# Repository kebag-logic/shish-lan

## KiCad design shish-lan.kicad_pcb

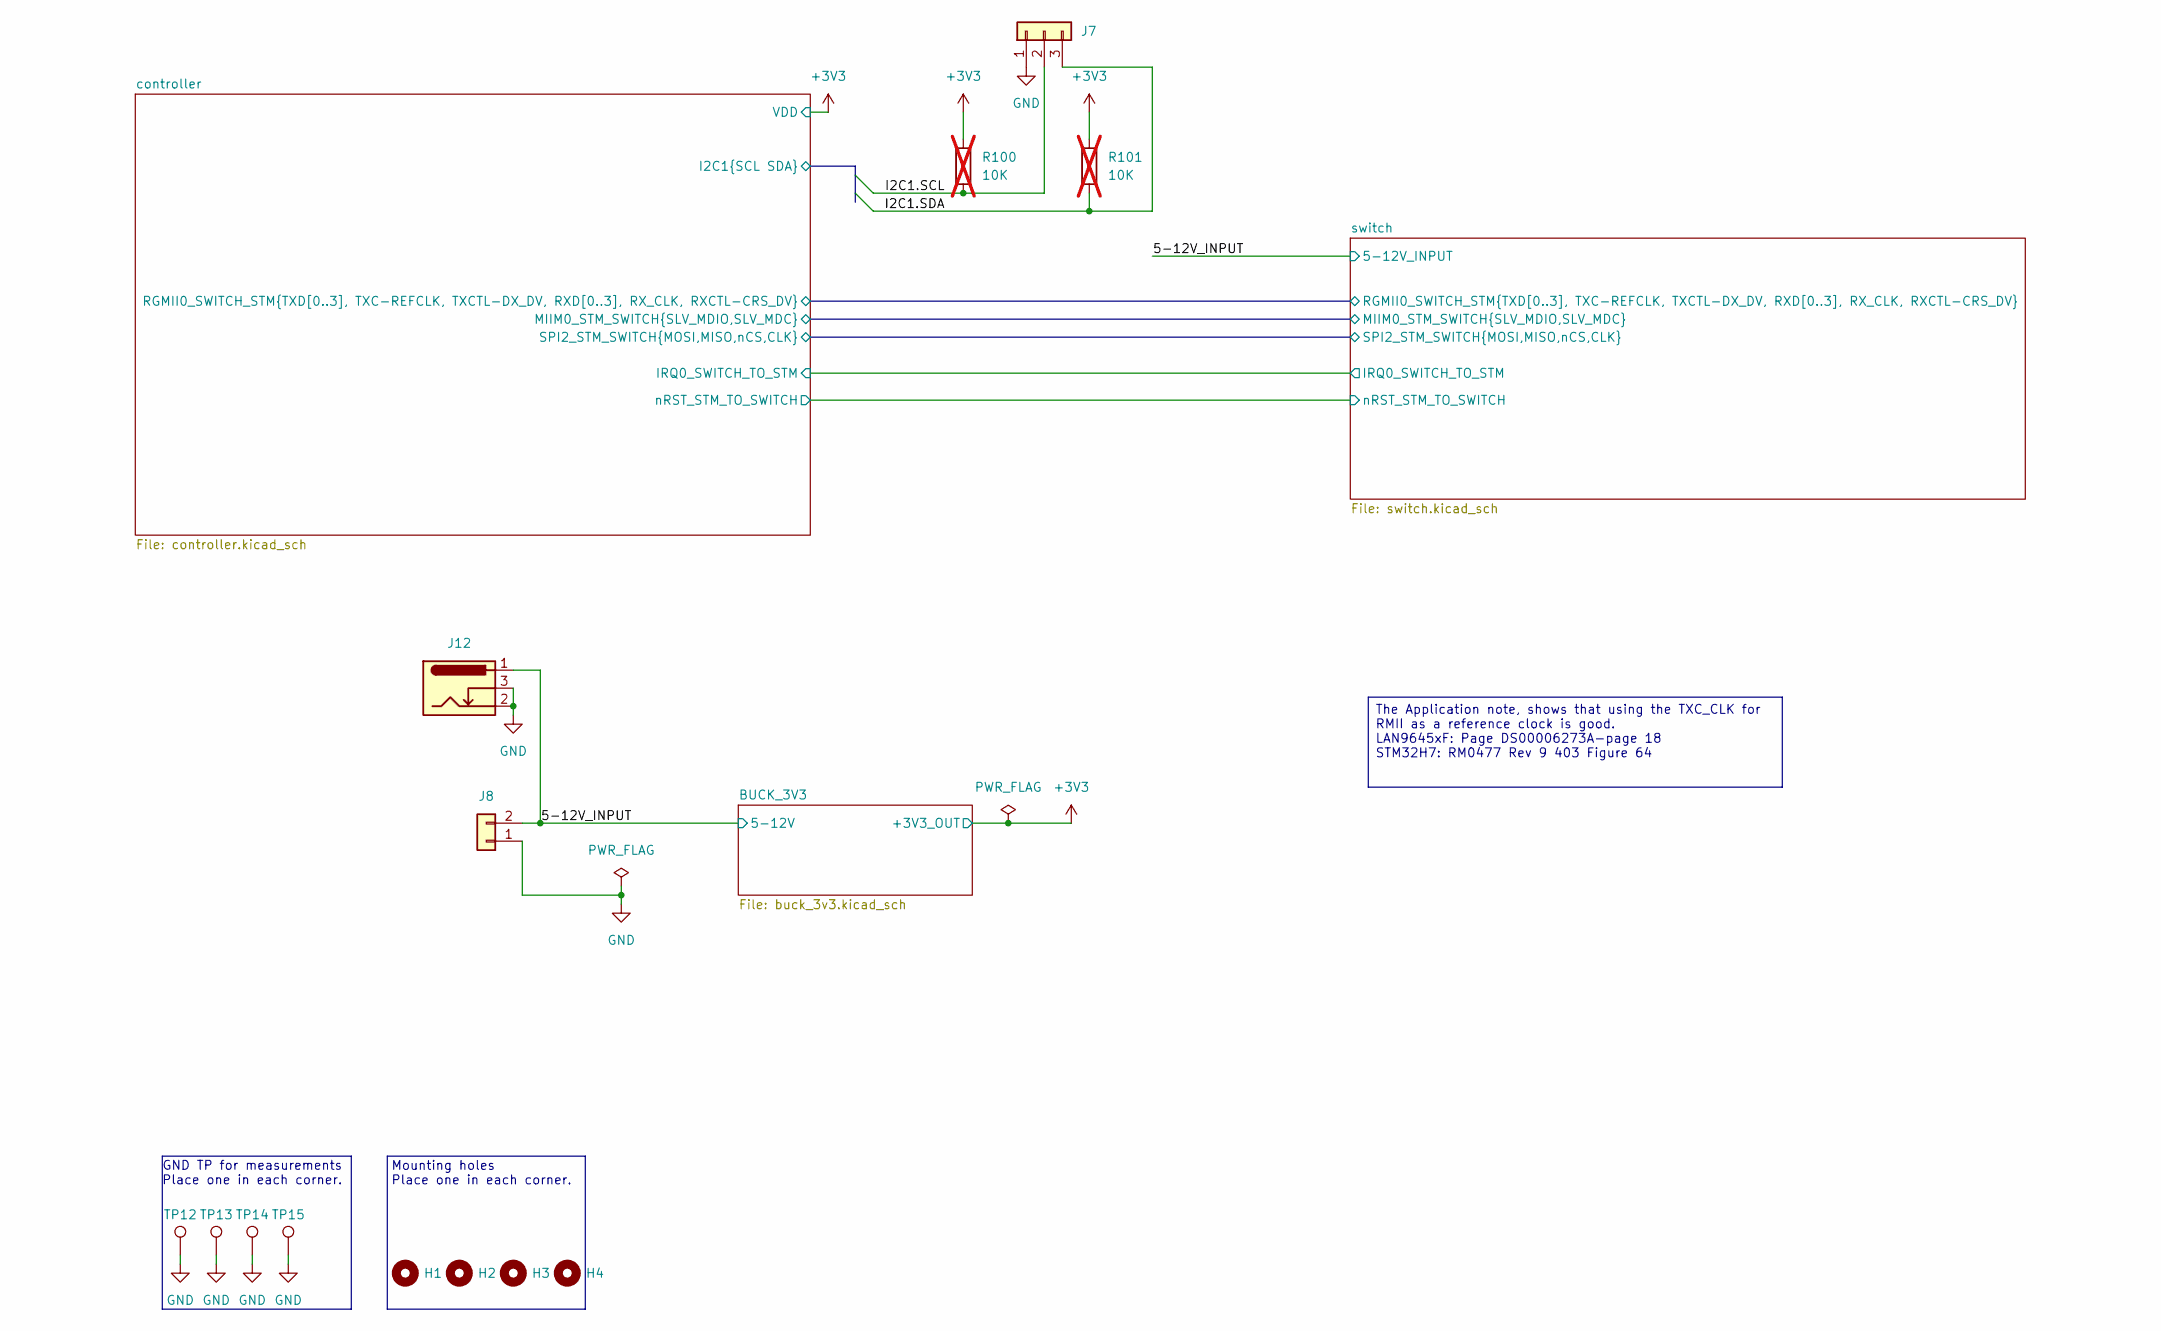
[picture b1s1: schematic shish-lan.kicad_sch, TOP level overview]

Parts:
H1, H2, H3, H4: MountingHole_M3; MountingHole_3.2mm_M3_Pad
J7: Header_03x01_2.54mm_0mm_Straight; 03x01_2.54mm_Header; MPN 87224-3; Mouser 571-872243
J8: Header_02x01_2.54mm_0mm_Straight; 02x01_2.54mm_Header; MPN 87224-2; Mouser 571-872242
J12: DC-Jack_Wuerth_694108301002; MPN 694108301002; Mouser 710-694108301002
R100, R101: 10K; R_0603; Tolerance_in_pct 5; MPN CRCW060310K0JNEC; Mouser 71-CRCW060310K0JNEC; not fitted
TP12, TP13, TP14, TP15: TestPoint

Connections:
/5-12V_INPUT: J8.2, J12.1; also elsewhere on the board
/controller/I2C1.SCL: J7.2, R100.2; also elsewhere on the board
/controller/I2C1.SDA: J7.3, R101.2; also elsewhere on the board

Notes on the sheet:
Mounting holes Place one in each corner.
GND TP for measurements Place one in each corner.
The Application note, shows that using the TXC_CLK for RMII as a reference clock is good. LAN9645xF: Page DS00006273A-page 18 STM32H7: RM0477 Rev 9 403 Figure 64

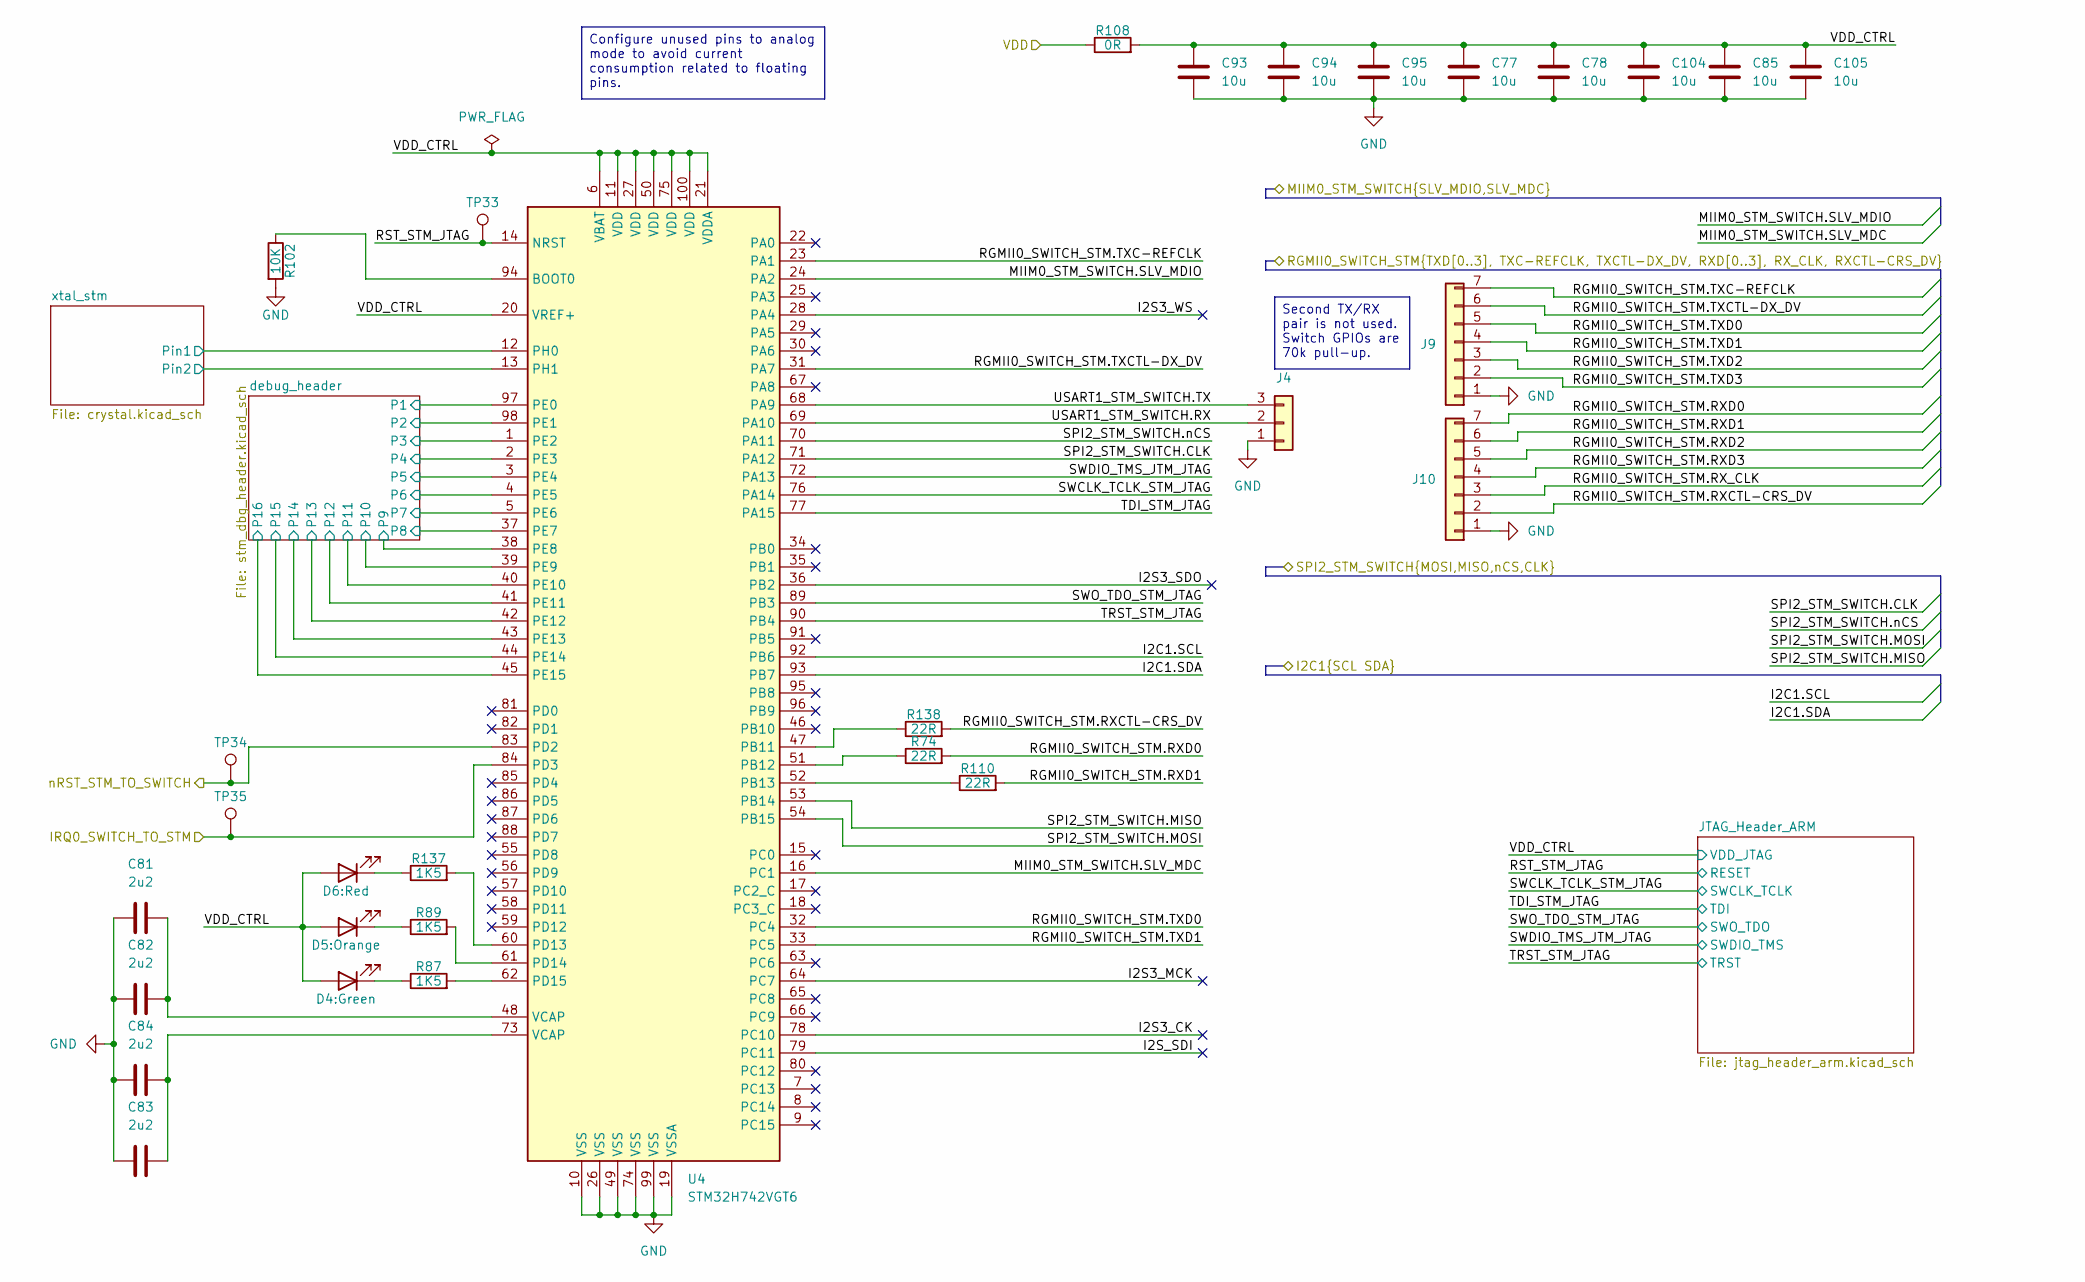
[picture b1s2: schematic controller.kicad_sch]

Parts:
C77, C78, C85, C93, C94, C95, C104, C105: 10u; C_0603; Voltage_in_V 25; Tolerance_in_pct 20; MPN CL10A106MA8NRNC; Mouser 187-CL10A106MA8NRNC
C81, C82, C83, C84: 2u2; C_0603; Voltage_in_V 35; Tolerance_in_pct 20; MPN GRM188R6YA225MA12D; Mouser 81-GRM188R6YA225MA2D
D4: LED_{color}_{U_F}_{I_F}; LED_0603; MPN LTST-C190GKT; Mouser 859-LTST-C190GKT
D5: LED_{color}_{U_F}_{I_F}; LED_0603; MPN LTST-C190KFKT; Mouser 859-LTST-C190KFKT
D6: LED_{color}_{U_F}_{I_F}; LED_0603; MPN LTST-C194KRKT; Mouser 859-LTST-C194KRKT
J4: Header_03x01_2.54mm_0mm_Straight; 03x01_2.54mm_Header; MPN 87224-3; Mouser 571-872243
J9, J10: Header_07x01_2.54mm_0mm_Straight; 07x01_2.54mm_Header; MPN TLW-107-06-G-S; Mouser 200-TLW10706GS
R74, R110, R138: 22R; R_0603; Tolerance_in_pct 1; MPN RC0603FR-1022RL; Mouser 603-RC0603FR-1022RL
R87, R89, R137: 1K5; R_0603; Tolerance_in_pct 5; MPN AC0603JR-071K5L; Mouser 603-AC0603JR-071K5L
R102: 10K; R_0603; Tolerance_in_pct 5; MPN CRCW060310K0JNEC; Mouser 71-CRCW060310K0JNEC
R108: 0R; R_2512; Tolerance_in_pct 5; MPN CRF2512-J/-000ELF; Mouser 652-CRF2512-J-000ELF
TP33, TP34, TP35: TestPoint
U4: STM32H742VGT6; LQFP-100_14x14mm_P0.5mm; MPN STM32H742VGT6; Mouser 511-STM32H742VGT6

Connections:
/controller/I2C1.SCL: U4.92 (PB6); also elsewhere on the board
/controller/I2C1.SDA: U4.93 (PB7); also elsewhere on the board
/controller/I2S3_CK: U4.78 (PC10)
/controller/I2S3_MCK: U4.64 (PC7)
/controller/I2S3_SDO: U4.36 (PB2)
/controller/I2S3_WS: U4.28 (PA4)
/controller/I2S_SDI: U4.79 (PC11)
/controller/MIIM0_STM_SWITCH.SLV_MDC: U4.16 (PC1); also elsewhere on the board
/controller/MIIM0_STM_SWITCH.SLV_MDIO: U4.24 (PA2); also elsewhere on the board
/controller/RGMII0_SWITCH_STM.RXCTL-CRS_DV: J10.2, R138.2; also elsewhere on the board
/controller/RGMII0_SWITCH_STM.RXD0: J10.7 (Pin_3), R74.2; also elsewhere on the board
/controller/RGMII0_SWITCH_STM.RXD1: J10.6 (Pin_3), R110.2; also elsewhere on the board
/controller/RGMII0_SWITCH_STM.RXD2: J10.5 (Pin_2); also elsewhere on the board
/controller/RGMII0_SWITCH_STM.RXD3: J10.4 (Pin_1); also elsewhere on the board
/controller/RGMII0_SWITCH_STM.RX_CLK: J10.3; also elsewhere on the board
/controller/RGMII0_SWITCH_STM.TXC-REFCLK: J9.7 (Pin_3), U4.23 (PA1); also elsewhere on the board
/controller/RGMII0_SWITCH_STM.TXCTL-DX_DV: J9.6 (Pin_3), U4.31 (PA7); also elsewhere on the board
/controller/RGMII0_SWITCH_STM.TXD0: J9.5 (Pin_2), U4.32 (PC4); also elsewhere on the board
/controller/RGMII0_SWITCH_STM.TXD1: J9.4 (Pin_1), U4.33 (PC5); also elsewhere on the board
/controller/RGMII0_SWITCH_STM.TXD2: J9.3; also elsewhere on the board
/controller/RGMII0_SWITCH_STM.TXD3: J9.2; also elsewhere on the board
/controller/RST_STM_JTAG: TP33.1 (1_1), U4.14 (NRST); also elsewhere on the board
/controller/SPI2_STM_SWITCH.CLK: U4.71 (PA12); also elsewhere on the board
/controller/SPI2_STM_SWITCH.MISO: U4.53 (PB14); also elsewhere on the board
/controller/SPI2_STM_SWITCH.MOSI: U4.54 (PB15); also elsewhere on the board
/controller/SPI2_STM_SWITCH.nCS: U4.70 (PA11); also elsewhere on the board
/controller/SWCLK_TCLK_STM_JTAG: U4.76 (PA14); also elsewhere on the board
/controller/SWDIO_TMS_JTM_JTAG: U4.72 (PA13); also elsewhere on the board
/controller/SWO_TDO_STM_JTAG: U4.89 (PB3); also elsewhere on the board
/controller/TDI_STM_JTAG: U4.77 (PA15); also elsewhere on the board
/controller/TRST_STM_JTAG: U4.90 (PB4); also elsewhere on the board
/controller/USART1_STM_SWITCH.RX: J4.2, U4.69 (PA10)
/controller/USART1_STM_SWITCH.TX: J4.3, U4.68 (PA9)
/controller/VDD_CTRL: C77.1, C78.1, C85.1, C93.1, C94.1, C95.1, C104.1, C105.1, D4.2 (A), D5.2 (A), D6.2 (A), R108.2, U4.6 (VBAT), U4.11 (VDD), U4.20 (VREF+), U4.21 (VDDA), U4.27 (VDD), U4.50 (VDD), U4.75 (VDD), U4.100 (VDD); also elsewhere on the board
/controller/debug_header/P1: U4.97 (PE0); also elsewhere on the board
/controller/debug_header/P2: U4.98 (PE1); also elsewhere on the board
/controller/debug_header/P3: U4.1 (PE2); also elsewhere on the board
/controller/debug_header/P4: U4.2 (PE3); also elsewhere on the board
/controller/debug_header/P5: U4.3 (PE4); also elsewhere on the board
/controller/debug_header/P6: U4.4 (PE5); also elsewhere on the board
/controller/debug_header/P7: U4.5 (PE6); also elsewhere on the board
/controller/debug_header/P8: U4.37 (PE7); also elsewhere on the board
/controller/debug_header/P9: U4.38 (PE8); also elsewhere on the board
/controller/debug_header/P10: U4.39 (PE9); also elsewhere on the board
/controller/debug_header/P11: U4.40 (PE10); also elsewhere on the board
/controller/debug_header/P12: U4.41 (PE11); also elsewhere on the board
/controller/debug_header/P13: U4.42 (PE12); also elsewhere on the board
/controller/debug_header/P14: U4.43 (PE13); also elsewhere on the board
/controller/debug_header/P15: U4.44 (PE14); also elsewhere on the board
/controller/debug_header/P16: U4.45 (PE15); also elsewhere on the board
/controller/xtal_stm/Pin1: U4.12 (PH0); also elsewhere on the board
/controller/xtal_stm/Pin2: U4.13 (PH1); also elsewhere on the board
/switch/IRQ0_SWITCH_TO_STM: TP35.1 (1_1), U4.84 (PD3); also elsewhere on the board
/switch/nRST_STM_TO_SWITCH: TP34.1 (1_1), U4.83 (PD2); also elsewhere on the board
unnamed: C81.2, C82.2, U4.48 (VCAP)
unnamed: C83.2, C84.2, U4.73 (VCAP)
unnamed: D4.1 (K), R87.1
unnamed: D5.1 (K), R89.1
unnamed: D6.1 (K), R137.1
unnamed: R102.1, U4.94 (BOOT0)
unnamed: R138.1, U4.47 (PB11)
unnamed: R74.1, U4.51 (PB12)
unnamed: R110.1, U4.52 (PB13)
unnamed: R137.2, U4.60 (PD13)
unnamed: R89.2, U4.61 (PD14)
unnamed: R87.2, U4.62 (PD15)

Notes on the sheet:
Second TX/RX pair is not used. Switch GPIOs are 70k pull-up.
Configure unused pins to analog mode to avoid current consumption related to floating pins.

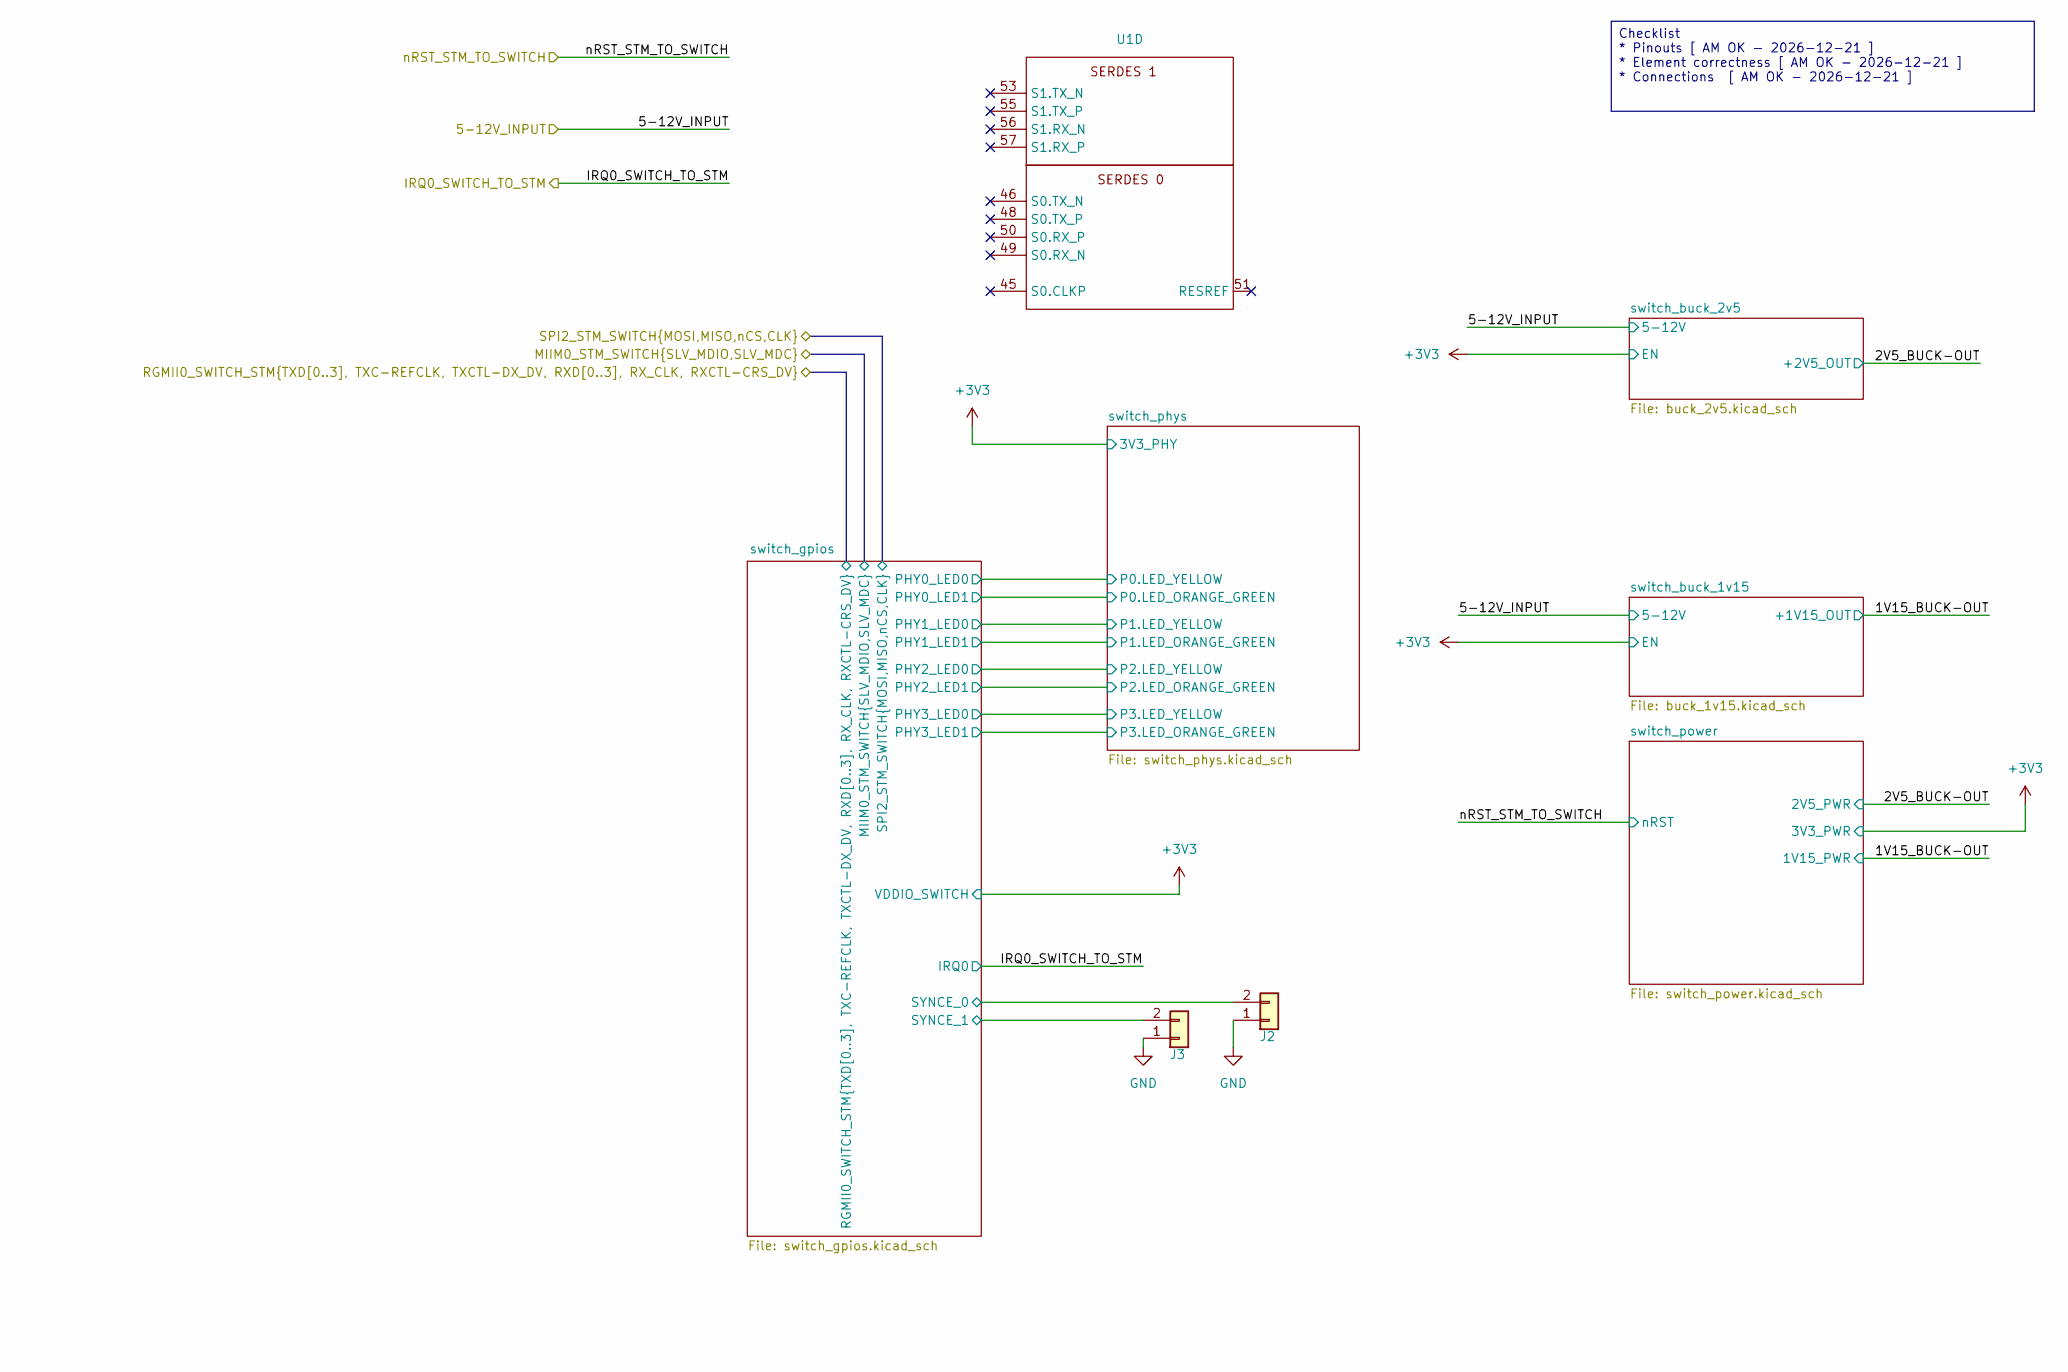
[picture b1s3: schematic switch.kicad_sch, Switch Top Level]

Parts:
J2, J3: Header_02x01_2.54mm_0mm_Straight; 02x01_2.54mm_Header; MPN 87224-2; Mouser 571-872242
U1: LAN96455F-I/8MW; TQFP-128_14x14mm_P0.4mm; MPN LAN96455F-I/8MW; Mouser 579-LAN96455FI8MW

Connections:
/switch/switch_gpios/SYNCE_0: J2.2; also elsewhere on the board
/switch/switch_gpios/SYNCE_1: J3.2; also elsewhere on the board

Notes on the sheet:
Checklist * Pinouts [ AM OK - 2026-12-21 ] * Element correctness [ AM OK - 2026-12-21 ] * Connections [ AM OK - 2026-12-21 ]

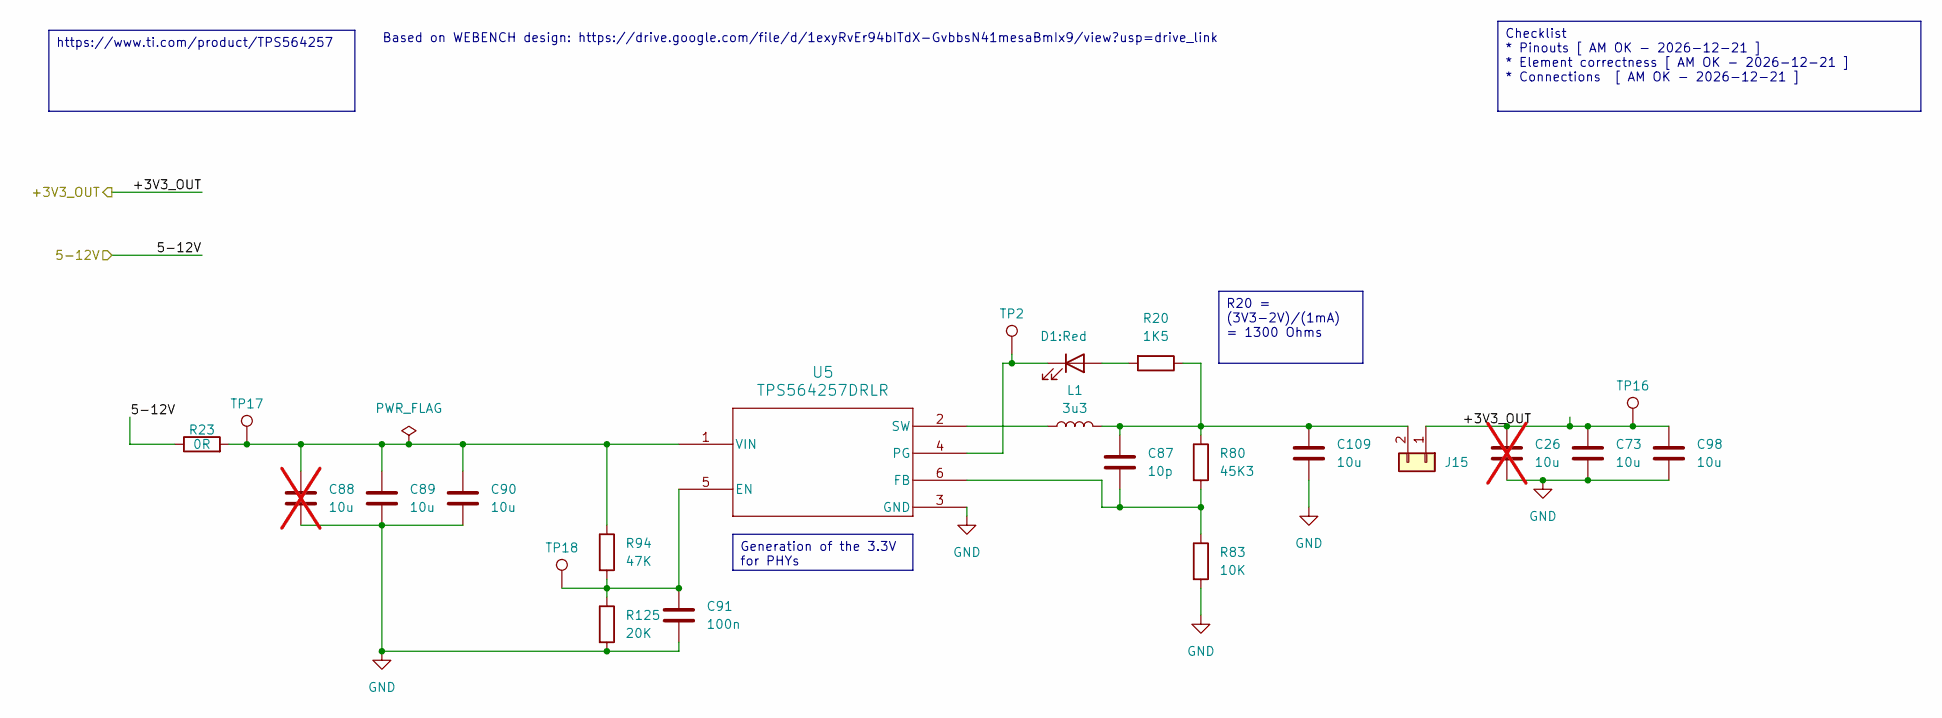
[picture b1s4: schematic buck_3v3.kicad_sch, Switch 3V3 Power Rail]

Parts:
C26, C88: 10u; C_0603; Voltage_in_V 25; Tolerance_in_pct 20; MPN CL10A106MA8NRNC; Mouser 187-CL10A106MA8NRNC; not fitted
C73, C89, C90, C98, C109: 10u; C_0603; Voltage_in_V 25; Tolerance_in_pct 20; MPN CL10A106MA8NRNC; Mouser 187-CL10A106MA8NRNC
C87: 10p; C_0603; Voltage_in_V 25; Tolerance_in_pct 5; MPN CC0603JRNPO8BN100; Mouser 603-CC0603JRNP8BN100
C91: 100n; C_0603; Voltage_in_V 50; Tolerance_in_pct 10; MPN CL10B104KB8NNNC; Mouser 187-CL10B104KB8NNNC
D1: LED_{color}_{U_F}_{I_F}; LED_0603; MPN LTST-C194KRKT; Mouser 859-LTST-C194KRKT
J15: Header_02x01_2.54mm_0mm_Straight; 02x01_2.54mm_Header; MPN 87224-2; Mouser 571-872242
L1: 3u3; EXLA1V0603; Tolerance_in_pct 20; MPN EXLA1V0603-3R3-R; Digikey 283-EXLA1V0603-3R3-RCT-ND
R20: 1K5; R_0603; Tolerance_in_pct 5; MPN AC0603JR-071K5L; Mouser 603-AC0603JR-071K5L
R23: 0R; R_2512; Tolerance_in_pct 5; MPN CRF2512-J/-000ELF; Mouser 652-CRF2512-J-000ELF
R80: 45K3; R_0603; Tolerance_in_pct 1; MPN RC0603FR-0745K3L; Mouser 603-RC0603FR-0745K3L
R83: 10K; R_0603; Tolerance_in_pct 1; MPN RC0603FR-0710KL; Mouser 603-RC0603FR-0710KL
R94: 47K; R_0603; Tolerance_in_pct 1; MPN RC0603FR-0747KP; Mouser 603-RC0603FR-0747KP
R125: 20K; R_0603; Tolerance_in_pct 1; MPN RC0603FR-1320KL; Mouser 603-RC0603FR-1320KL
TP2, TP16, TP17, TP18: TestPoint
U5: TPS564257DRLR; SOT-563; MPN TPS564257DRLR; Mouser 595-TPS564257DRLR

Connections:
/5-12V_INPUT: R23.1; also elsewhere on the board
unnamed: D1.2 (A), R20.2
unnamed: D1.1 (K), TP2.1 (1_1), U5.4 (PG)
unnamed: C87.1, C109.1, J15.2, L1.2, R20.1, R80.1
unnamed: C91.1, R94.2, R125.1, TP18.1 (1_1), U5.5 (EN)
unnamed: C87.2, R80.2, R83.1, U5.6 (FB)
unnamed: L1.1, U5.2 (SW)
unnamed: C88.1, C89.1, C90.1, R23.2, R94.1, TP17.1 (1_1), U5.1 (VIN)

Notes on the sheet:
Based on WEBENCH design: https://drive.google.com/file/d/1exyRvEr94bITdX-GvbbsN41mesaBmIx9/view?usp=drive_link
R20 = (3V3-2V)/(1mA) = 1300 Ohms
https://www.ti.com/product/TPS564257
Checklist * Pinouts [ AM OK - 2026-12-21 ] * Element correctness [ AM OK - 2026-12-21 ] * Connections [ AM OK - 2026-12-21 ]
Generation of the 3.3V for PHYs

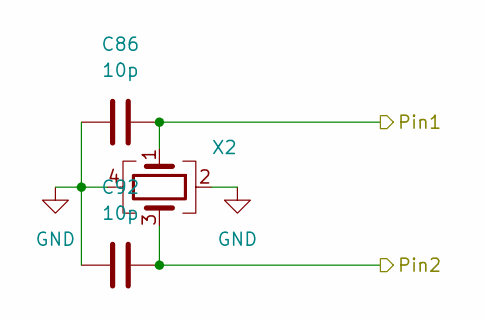
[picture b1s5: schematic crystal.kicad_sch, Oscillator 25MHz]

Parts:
C86, C92: 10p; C_0603; Voltage_in_V 25; Tolerance_in_pct 5; MPN CC0603JRNPO8BN100; Mouser 603-CC0603JRNP8BN100
X2: 25M; VXM7; MPN VXM7-9032-25M0000000; Digikey 150-VXM7-9032-25M0000000CT-ND

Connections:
/controller/xtal_stm/Pin1: C86.1, X2.1; also elsewhere on the board
/controller/xtal_stm/Pin2: C92.1, X2.3; also elsewhere on the board

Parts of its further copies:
C22, C23: 10p; C_0603; Voltage_in_V 25; Tolerance_in_pct 5; MPN CC0603JRNPO8BN100; Mouser 603-CC0603JRNP8BN100
X1: 25M; VXM7; MPN VXM7-9032-25M0000000; Digikey 150-VXM7-9032-25M0000000CT-ND

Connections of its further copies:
/switch/switch_power/xtal_switch/Pin1: C22.1, X1.1; also elsewhere on the board
/switch/switch_power/xtal_switch/Pin2: C23.1, X1.3; also elsewhere on the board

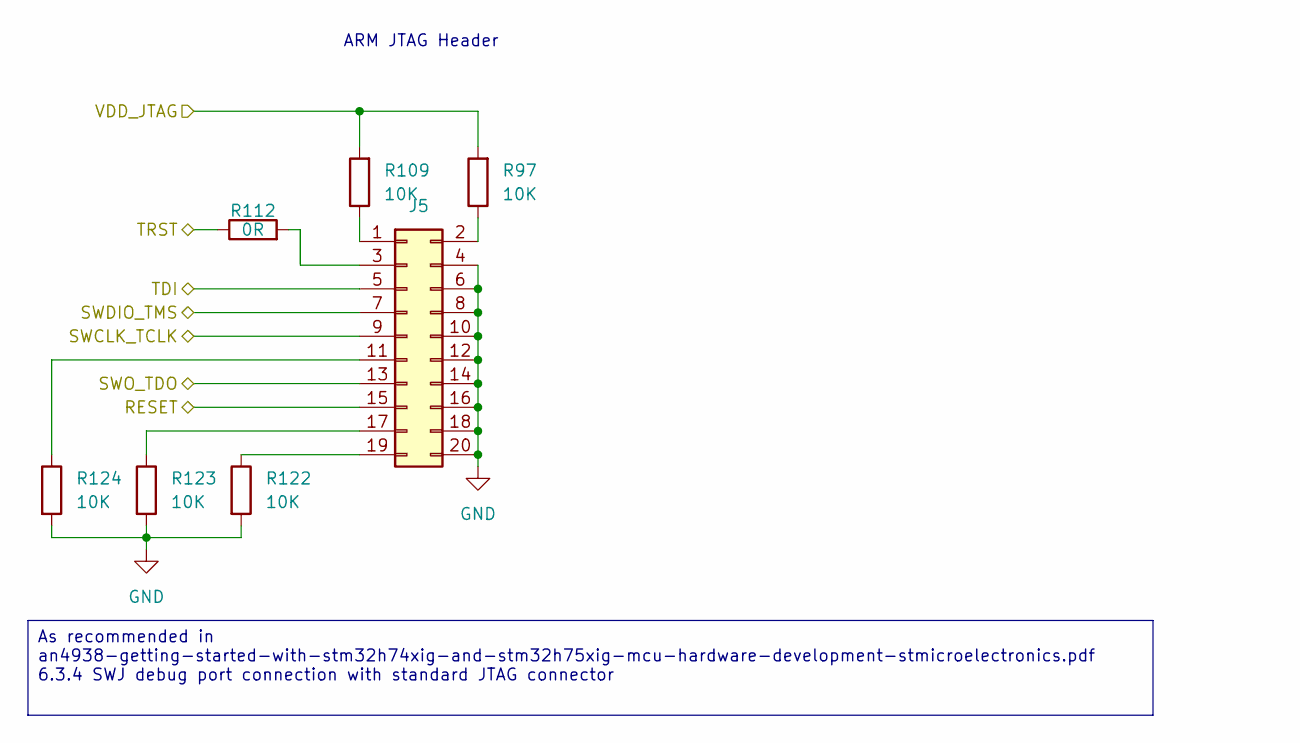
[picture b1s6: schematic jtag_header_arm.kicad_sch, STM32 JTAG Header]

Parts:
J5: Header_10x02_2.54mm_2.54mm_Straight; 10x02_2.54mm_Header; MPN BHR-20-VUA; Mouser 737-BHR-20-VUA
R97, R109, R122, R123, R124: 10K; R_0603; Tolerance_in_pct 5; MPN CRCW060310K0JNEC; Mouser 71-CRCW060310K0JNEC
R112: 0R; R_0603; Tolerance_in_pct 5; MPN RC0603JR-070RP; Mouser 603-RC0603JR-070RP

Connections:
/controller/RST_STM_JTAG: J5.15; also elsewhere on the board
/controller/SWCLK_TCLK_STM_JTAG: J5.9; also elsewhere on the board
/controller/SWDIO_TMS_JTM_JTAG: J5.7; also elsewhere on the board
/controller/SWO_TDO_STM_JTAG: J5.13; also elsewhere on the board
/controller/TDI_STM_JTAG: J5.5; also elsewhere on the board
/controller/TRST_STM_JTAG: R112.1; also elsewhere on the board
/controller/VDD_CTRL: R97.2, R109.2; also elsewhere on the board
unnamed: J5.1, R109.1
unnamed: J5.2, R97.1
unnamed: J5.3, R112.2
unnamed: J5.11, R124.1
unnamed: J5.17, R123.1
unnamed: J5.19, R122.1

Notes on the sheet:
ARM JTAG Header
As recommended in an4938-getting-started-with-stm32h74xig-and-stm32h75xig-mcu-hardware-development-stmicroelectronics.pdf 6.3.4 SWJ debug port connection with standard JTAG connector

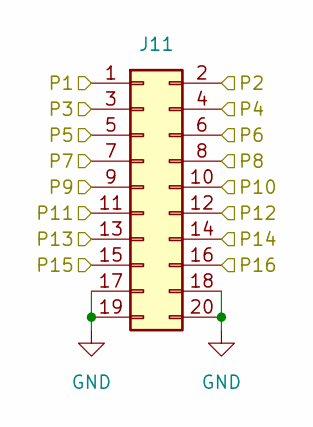
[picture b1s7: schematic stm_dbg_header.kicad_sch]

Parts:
J11: Header_10x02_2.54mm_2.54mm_Straight; 10x02_2.54mm_Header; MPN BHR-20-VUA; Mouser 737-BHR-20-VUA

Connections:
/controller/debug_header/P1: J11.1; also elsewhere on the board
/controller/debug_header/P2: J11.2; also elsewhere on the board
/controller/debug_header/P3: J11.3; also elsewhere on the board
/controller/debug_header/P4: J11.4; also elsewhere on the board
/controller/debug_header/P5: J11.5; also elsewhere on the board
/controller/debug_header/P6: J11.6; also elsewhere on the board
/controller/debug_header/P7: J11.7; also elsewhere on the board
/controller/debug_header/P8: J11.8; also elsewhere on the board
/controller/debug_header/P9: J11.9; also elsewhere on the board
/controller/debug_header/P10: J11.10; also elsewhere on the board
/controller/debug_header/P11: J11.11; also elsewhere on the board
/controller/debug_header/P12: J11.12; also elsewhere on the board
/controller/debug_header/P13: J11.13; also elsewhere on the board
/controller/debug_header/P14: J11.14; also elsewhere on the board
/controller/debug_header/P15: J11.15; also elsewhere on the board
/controller/debug_header/P16: J11.16; also elsewhere on the board

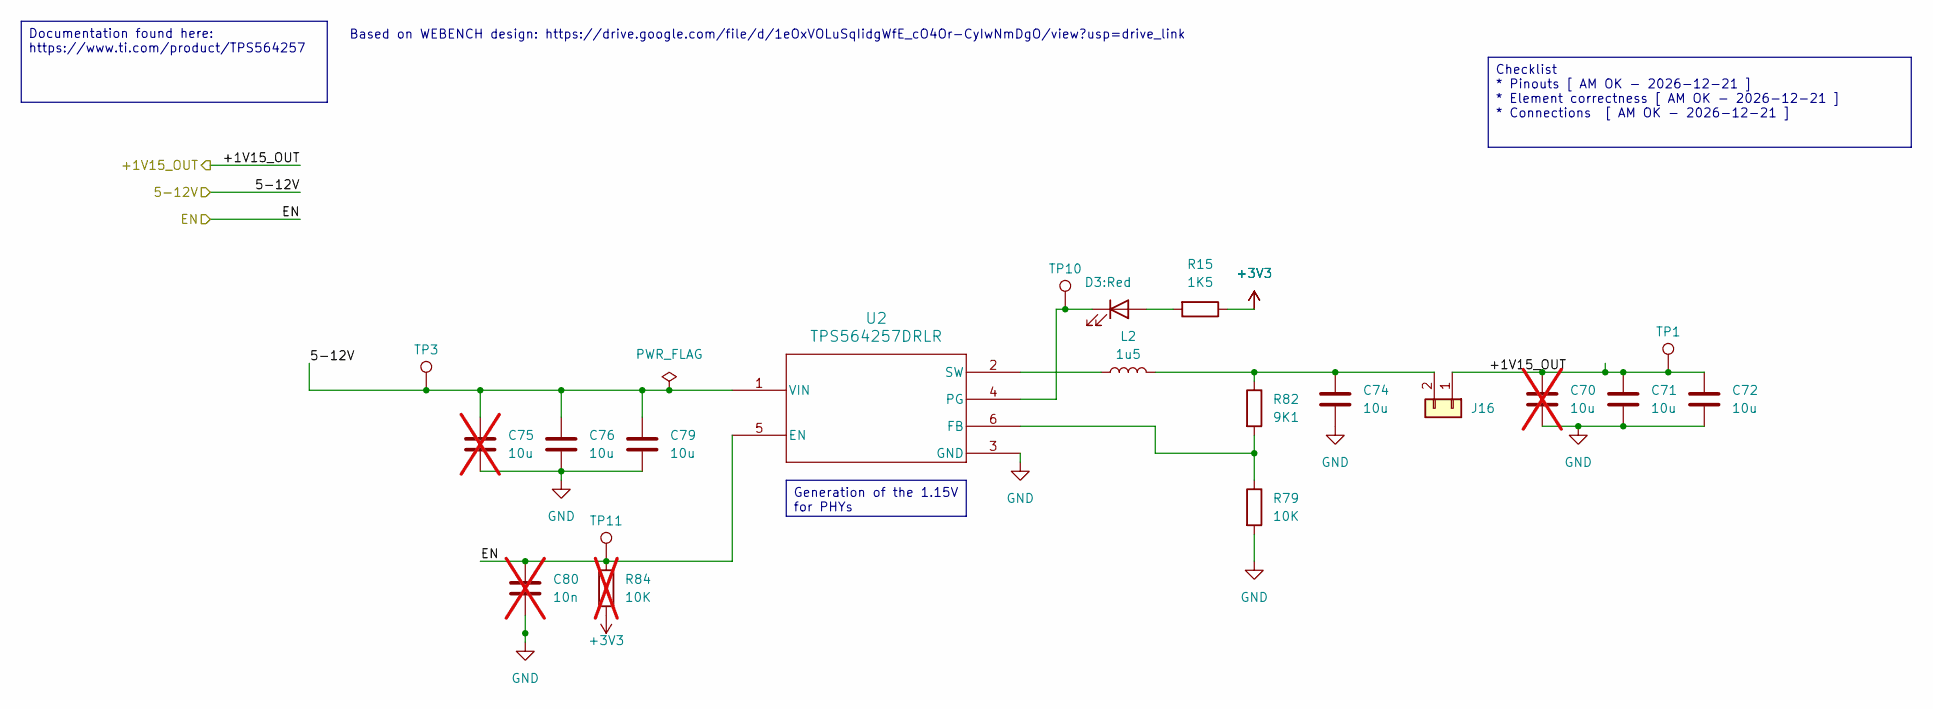
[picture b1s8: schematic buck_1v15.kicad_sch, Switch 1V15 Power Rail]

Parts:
C70, C75: 10u; C_0603; Voltage_in_V 25; Tolerance_in_pct 20; MPN CL10A106MA8NRNC; Mouser 187-CL10A106MA8NRNC; not fitted
C71, C72, C74, C76, C79: 10u; C_0603; Voltage_in_V 25; Tolerance_in_pct 20; MPN CL10A106MA8NRNC; Mouser 187-CL10A106MA8NRNC
C80: 10n; C_0603; Voltage_in_V 50; Tolerance_in_pct 10; MPN CL10B103KB8WPND; Mouser 187-CL10B103KB8WPND; not fitted
D3: LED_{color}_{U_F}_{I_F}; LED_0603; MPN LTST-C194KRKT; Mouser 859-LTST-C194KRKT
J16: Header_02x01_2.54mm_0mm_Straight; 02x01_2.54mm_Header; MPN 87224-2; Mouser 571-872242
L2: 1u5; SRP7050WA-1R5M; Tolerance_in_pct 20; MPN SRP7050WA-1R5M; Digikey 118-SRP7050WA-1R5MCT-ND
R15: 1K5; R_0603; Tolerance_in_pct 5; MPN AC0603JR-071K5L; Mouser 603-AC0603JR-071K5L
R79: 10K; R_0603; Tolerance_in_pct 5; MPN CRCW060310K0JNEC; Mouser 71-CRCW060310K0JNEC
R82: 9K1; R_0603; Tolerance_in_pct 1; MPN RC0603FR-079K1L; Mouser 603-RC0603FR-079K1L
R84: 10K; R_0603; Tolerance_in_pct 5; MPN CRCW060310K0JNEC; Mouser 71-CRCW060310K0JNEC; not fitted
TP1, TP3, TP10, TP11: TestPoint
U2: TPS564257DRLR; SOT-563; MPN TPS564257DRLR; Mouser 595-TPS564257DRLR

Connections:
/5-12V_INPUT: C75.1, C76.1, C79.1, TP3.1 (1_1), U2.1 (VIN); also elsewhere on the board
/switch/1V15_BUCK-OUT: C70.1, C71.1, C72.1, J16.1, TP1.1 (1_1); also elsewhere on the board
unnamed: D3.2 (A), R15.2
unnamed: D3.1 (K), TP10.1 (1_1), U2.4 (PG)
unnamed: C74.1, J16.2, L2.2, R82.1
unnamed: R79.1, R82.2, U2.6 (FB)
unnamed: L2.1, U2.2 (SW)

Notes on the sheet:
Based on WEBENCH design: https://drive.google.com/file/d/1eOxVOLuSqIidgWfE_cO4Or-CyIwNmDgO/view?usp=drive_link
Documentation found here: https://www.ti.com/product/TPS564257
Generation of the 1.15V for PHYs
Checklist * Pinouts [ AM OK - 2026-12-21 ] * Element correctness [ AM OK - 2026-12-21 ] * Connections [ AM OK - 2026-12-21 ]
